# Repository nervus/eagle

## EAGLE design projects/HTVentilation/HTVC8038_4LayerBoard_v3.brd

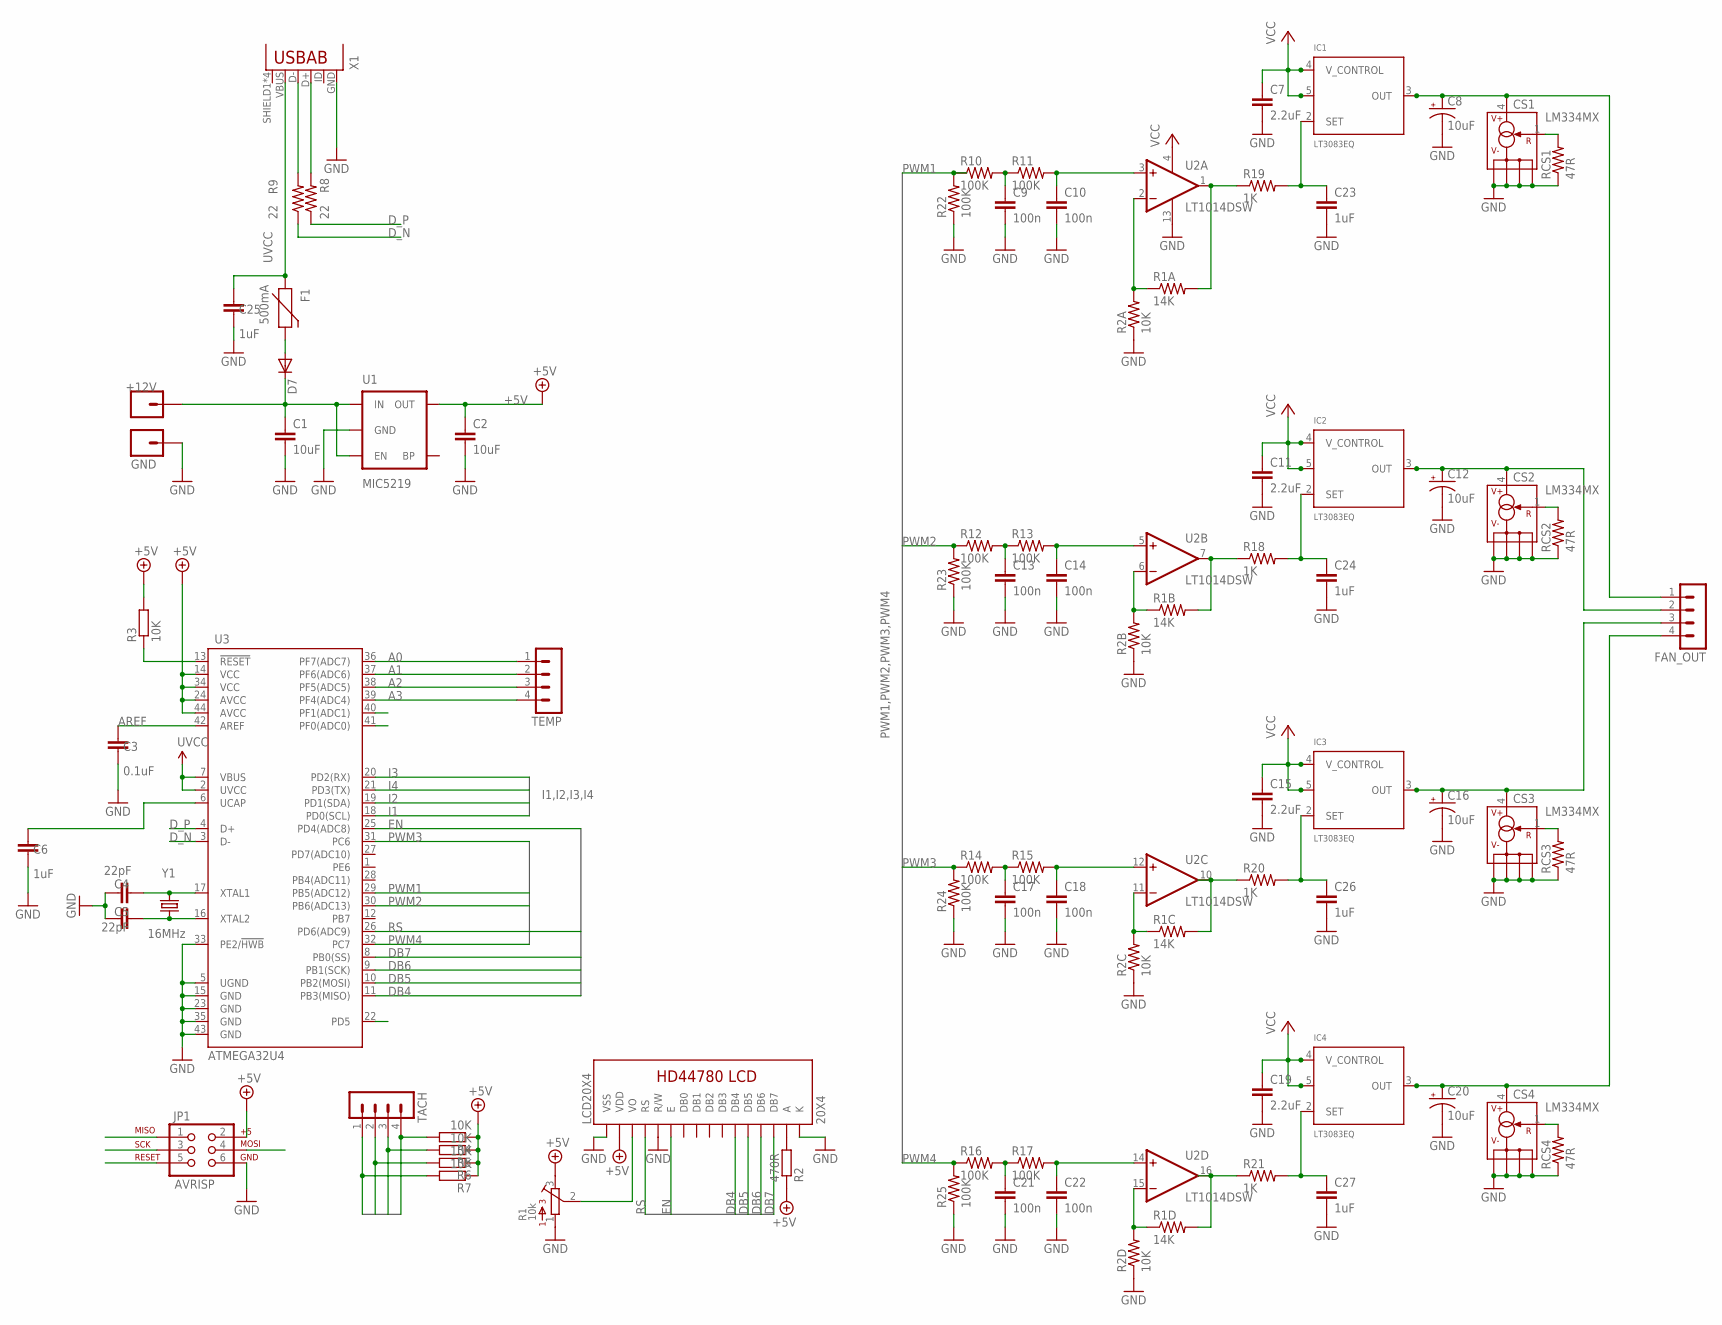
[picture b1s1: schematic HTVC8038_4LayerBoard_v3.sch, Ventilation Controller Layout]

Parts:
+12V: +12V; 1X01
C1, C2: 10uF; C1206
C3: 0.1uF; C0805
C4, C5: 22pF; C0805
C6, C23, C24, C25, C26, C27: 1uF; C0805
C7, C11, C15, C19: 2.2uF; C1206
C8, C12, C16, C20: 10uF; CT3528
C9, C10, C13, C14, C17, C18, C21, C22: 100n; C0805
CS1, CS2, CS3, CS4: LM334MX; SO08
D7: DIODESOD; SOD-323
F1: 500mA; PTC-1206
FAN_OUT: MA04-1
GND: GND; 1X01
IC1, IC2, IC3, IC4: LT3083EQ; DDPAK_TO263-5
JP1: AVRISP; 2X3-NS
LCD20X4: 20X4; LCD-20X4-4HOLES
R1: 10k; 3362P
R1A, R1B, R1C, R1D: 14K; R0603
R2: 470R; R0805
R2A, R2B, R2C, R2D, R3, R4, R5, R6, R7: 10K; R0805
R8, R9: 22; R0603
R10, R11, R12, R13, R14, R15, R16, R17, R22, R23, R24, R25: 100K; R0805
R18, R19, R20, R21: 1K; R0805
RCS1, RCS2, RCS3, RCS4: 47R; R0805
TACH: MA04-1
TEMP: MA04-1
U1: MIC5219; SOT23-5
U2: LT1014DSW; SO16W
U3: ATMEGA32U4; SPARKFUN-DIGITALIC_TQFP44
X1: USB-AB; USB-AB-MICRO-SMD
Y1: 16MHz; CRYSTAL-SMD-5X3

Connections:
+5V: C2.1, JP1.2, LCD20X4.P$2 (VDD), R1.3, R2.1, R3.2, R4.1, R5.1, R6.1, R7.1, U1.5 (OUT), U3.14 (VCC), U3.24 (AVCC), U3.34 (VCC), U3.44 (AVCC)
A0: TEMP.1, U3.36 (PF7(ADC7))
A1: TEMP.2, U3.37 (PF6(ADC6))
A2: TEMP.3, U3.38 (PF5(ADC5))
A3: TEMP.4, U3.39 (PF4(ADC4))
A4: U3.40 (PF1(ADC1))
A5: U3.41 (PF0(ADC0))
AREF: C3.2, U3.42 (AREF)
DB4: JP1.1, LCD20X4.P$11 (DB4), U3.11 (PB3(MISO))
DB5: JP1.4, LCD20X4.P$12 (DB5), U3.10 (PB2(MOSI))
DB6: JP1.3, LCD20X4.P$13 (DB6), U3.9 (PB1(SCK))
DB7: LCD20X4.P$14 (DB7), U3.8 (PB0(SS))
D_N: R9.1, U3.3 (D-)
D_P: R8.1, U3.4 (D+)
EN: LCD20X4.P$6 (E), U3.25 (PD4(ADC8))
GND: C1.2, C2.2, C3.1, C4.2, C5.2, C6.1, C7.2, C8.-, C9.2, C10.2, C11.2, C12.-, C13.2, C14.2, C15.2, C16.-, C17.2, C18.2, C19.2, C20.-, C21.2, C22.2, C23.2, C24.2, C25.1, C26.2, C27.2, CS1.2 (V-), CS1.3 (V-), CS1.6 (V-), CS1.7 (V-), CS2.2 (V-), CS2.3 (V-), CS2.6 (V-), CS2.7 (V-), CS3.2 (V-), CS3.3 (V-), CS3.6 (V-), CS3.7 (V-), CS4.2 (V-), CS4.3 (V-), CS4.6 (V-), CS4.7 (V-), GND.1, JP1.6, LCD20X4.P$1 (VSS), LCD20X4.P$5 (R/W), LCD20X4.P$16 (K), R1.1, R2A.1, R2B.1, R2C.1, R2D.1, R22.1, R23.1, R24.1, R25.1, RCS1.1, RCS2.1, RCS3.1, RCS4.1, U1.2 (GND), U2.13 (V-), U3.5 (UGND), U3.15 (GND), U3.23 (GND), U3.33 (PE2/!HWB), U3.35 (GND), U3.43 (GND), X1.GND
I1: R7.2, TACH.1, U3.18 (PD0(SCL))
I2: R6.2, TACH.2, U3.19 (PD1(SDA))
I3: R5.2, TACH.3, U3.20 (PD2(RX))
I4: R4.2, TACH.4, U3.21 (PD3(TX))
unnamed: R1A.1, R2A.2, U2.2 (-IN)
unnamed: R1B.1, R2B.2, U2.6 (-IN)
unnamed: R1C.1, R2C.2, U2.11 (-IN)
unnamed: R1D.1, R2D.2, U2.15 (-IN)
unnamed: C9.1, R10.2, R11.1
unnamed: C13.1, R12.2, R13.1
unnamed: LCD20X4.P$3 (VO), R1.2
unnamed: LCD20X4.P$15 (A), R2.2
unnamed: C5.1, U3.16 (XTAL2), Y1.1
unnamed: C4.1, U3.17 (XTAL1), Y1.3 (2)
unnamed: D7.2 (A), F1.2
unnamed: C6.2, U3.6 (UCAP)
unnamed: C17.1, R14.2, R15.1
unnamed: C21.1, R16.2, R17.1
unnamed: CS1.1 (R), RCS1.2
unnamed: CS2.1 (R), RCS2.2
unnamed: CS3.1 (R), RCS3.2
unnamed: CS4.1 (R), RCS4.2
unnamed: C27.1, IC4.2 (SET), R21.2
unnamed: C23.1, IC1.2 (SET), R19.2
unnamed: R1B.2, R18.1, U2.7 (OUT)
unnamed: C26.1, IC3.2 (SET), R20.2
OPAMP1: C10.1, R11.2, U2.3 (+IN)
OPAMP2: C14.1, R13.2, U2.5 (+IN)
OPAMP3: C18.1, R15.2, U2.12 (+IN)
OPAMP4: C22.1, R17.2, U2.14 (+IN)
OUT1: C8.+, CS1.4 (V+), FAN_OUT.1, IC1.3 (OUT), IC1.6 (OUT)
OUT2: C12.+, CS2.4 (V+), FAN_OUT.2, IC2.3 (OUT), IC2.6 (OUT)
OUT3: C16.+, CS3.4 (V+), FAN_OUT.3, IC3.3 (OUT), IC3.6 (OUT)
OUT4: C20.+, CS4.4 (V+), FAN_OUT.4, IC4.3 (OUT), IC4.6 (OUT)
PWM1: R10.1, R22.2, U3.29 (PB5(ADC12))
PWM2: R12.1, R23.2, U3.30 (PB6(ADC13))
PWM3: R14.1, R24.2, U3.31 (PC6)
PWM4: R16.1, R25.2, U3.32 (PC7)
RESET: JP1.5, R3.1, U3.13 (!RESET)
RS: LCD20X4.P$4 (RS), U3.26 (PD6(ADC9))
SET1: R1A.2, R19.1, U2.1 (OUT)
SET2: C24.1, IC2.2 (SET), R18.2
SET3: R1C.2, R20.1, U2.10 (OUT)
SET4: R1D.2, R21.1, U2.16 (OUT)
TXLED: U3.22 (PD5)
USB_N: R9.2, X1.D-
USB_P: R8.2, X1.D+
UVCC: C25.2, F1.1, U3.2 (UVCC), U3.7 (VBUS), X1.VBUS
VCC: +12V.1, C1.1, C7.1, C11.1, C15.1, C19.1, D7.1 (C), IC1.4 (V_CONTROL), IC1.5 (IN), IC2.4 (V_CONTROL), IC2.5 (IN), IC3.4 (V_CONTROL), IC3.5 (IN), IC4.4 (V_CONTROL), IC4.5 (IN), U1.1 (IN), U1.3 (EN), U2.4 (V+)

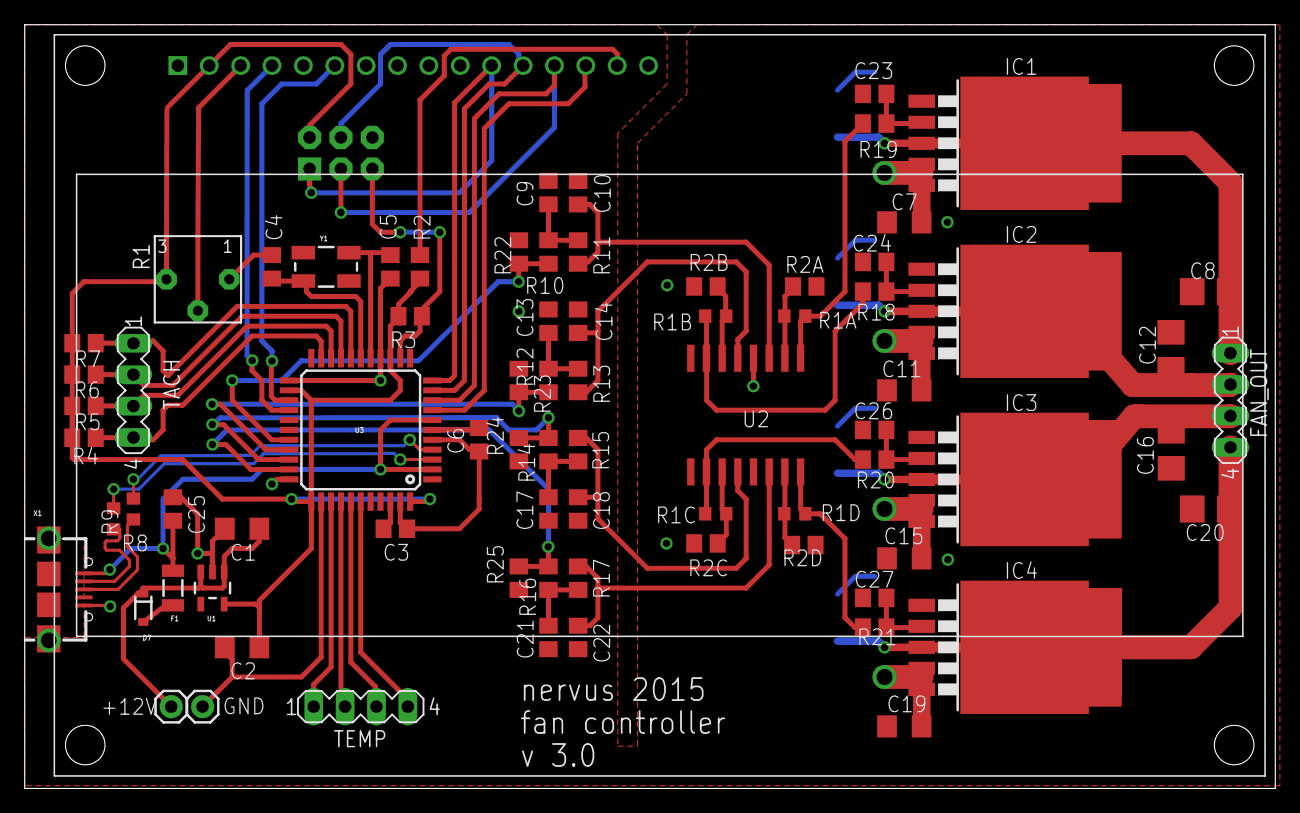
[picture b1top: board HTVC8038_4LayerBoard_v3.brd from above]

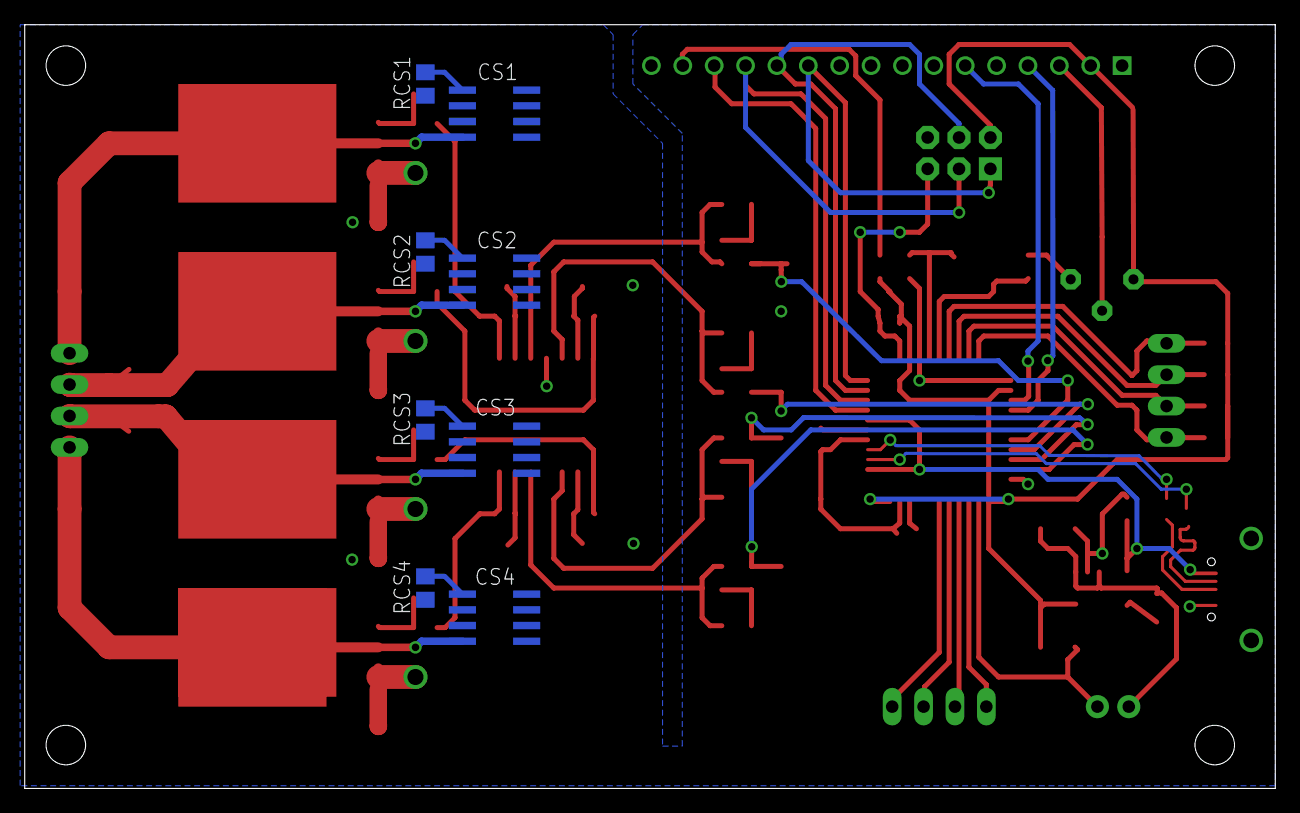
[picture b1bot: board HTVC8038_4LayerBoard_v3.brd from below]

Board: 4 copper layers, 101.2 x 61.8 mm, 86 parts (8 on the bottom side), 62 nets.

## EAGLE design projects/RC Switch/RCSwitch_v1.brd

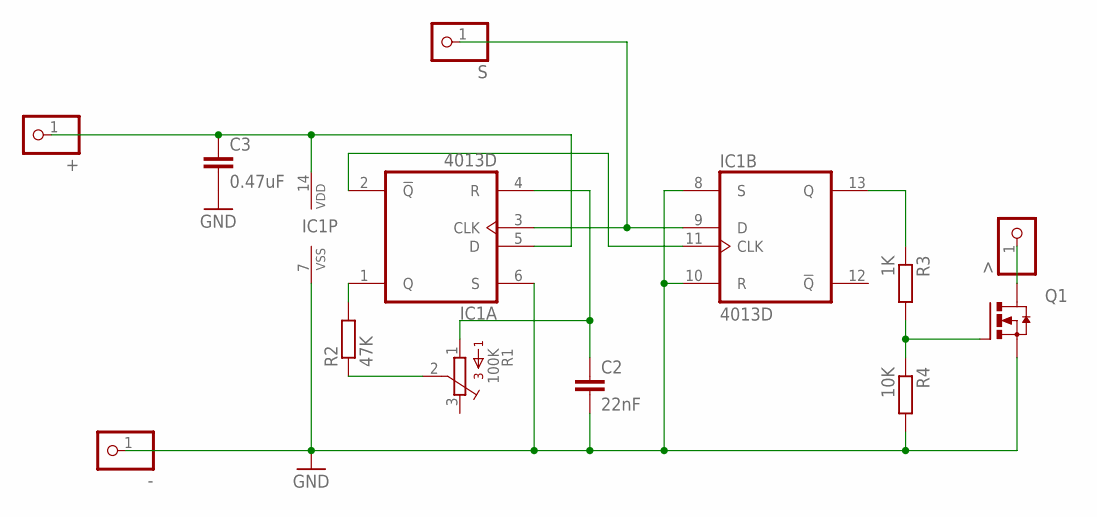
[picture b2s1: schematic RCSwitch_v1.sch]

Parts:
+: PINHD-1X1; 1X01
-: PINHD-1X1; 1X01
>: PINHD-1X1; 1X01
C2: 22nF; C3216
C3: 0.47uF; C3216
IC1: 4013D; SO14
Q1: IRF3704S; D2PACK
R1: 100K; 3386P
R2: 47K; R3225
R3: 1K; R3225
R4: 10K; R3225
S: PINHD-1X1; 1X01

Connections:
GND: -.1, C2.2, C3.2, IC1.6 (S), IC1.7 (VSS), IC1.8 (S), IC1.10 (R), Q1.3 (S), R4.2
unnamed: IC1.1 (Q), R2.2
unnamed: R1.2, R2.1
unnamed: C2.1, IC1.4 (R), R1.1
unnamed: IC1.13 (Q), R3.1
unnamed: IC1.3 (CLK), IC1.9 (D), S.1
unnamed: >.1, Q1.2 (D)
unnamed: IC1.2 (!Q), IC1.11 (CLK)
unnamed: +.1, C3.1, IC1.5 (D), IC1.14 (VDD)
OUTPUT: Q1.1 (G), R3.2, R4.1

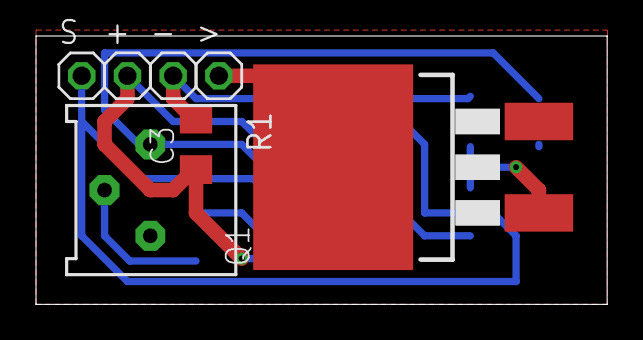
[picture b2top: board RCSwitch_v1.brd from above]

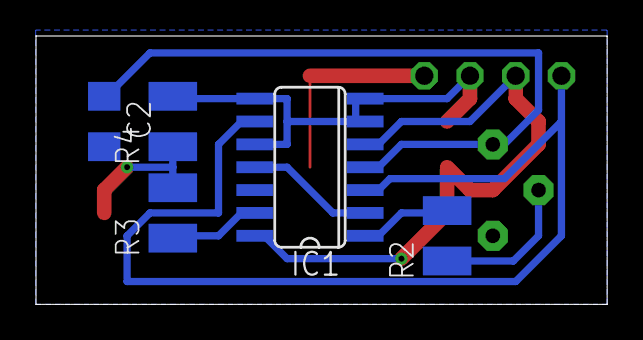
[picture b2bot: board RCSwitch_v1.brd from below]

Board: 2 copper layers, 31.7 x 14.9 mm, 12 parts (5 on the bottom side), 10 nets.

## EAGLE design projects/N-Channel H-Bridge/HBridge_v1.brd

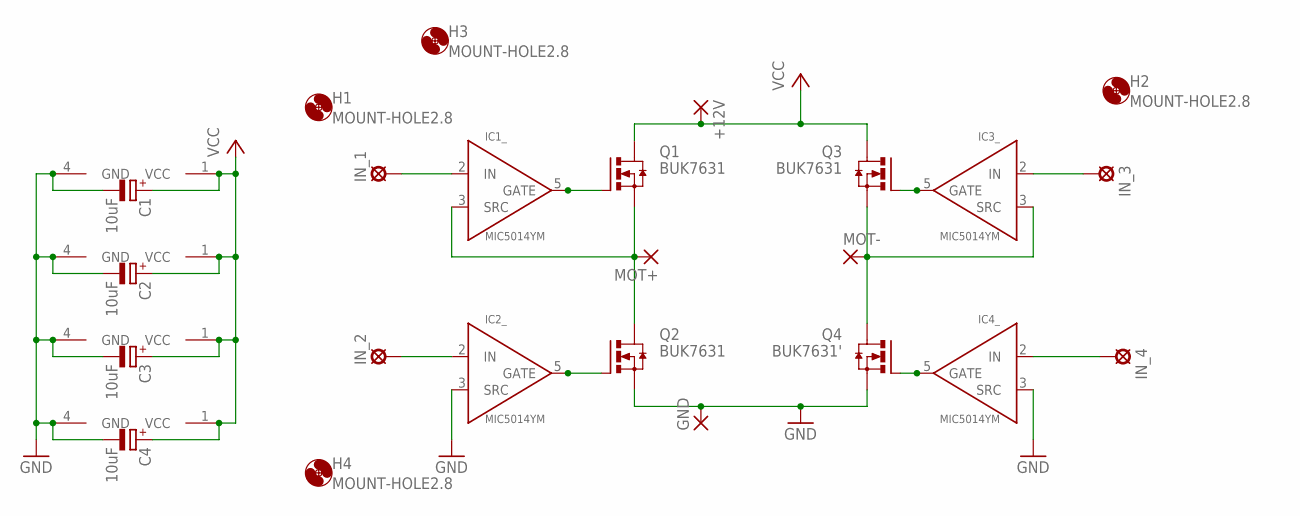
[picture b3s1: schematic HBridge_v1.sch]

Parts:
+12V: WIREPAD4,16O1,6; 4,16O1,6
C1, C2, C3, C4: 10uF; UD-4X5,8_NICHICON
GND: WIREPAD4,16O1,6; 4,16O1,6
H1, H2, H3, H4: MOUNT-HOLE2.8; 2,8
IC1, IC2, IC3, IC4: MIC5014YM; SO8
IN_1, IN_2, IN_3, IN_4: LSP11
MOT+: WIREPAD4,16O1,6; 4,16O1,6
MOT-: WIREPAD4,16O1,6; 4,16O1,6
Q1, Q2, Q3: BUK7631; D2PAK_TO263
Q4: BUK7631'; D2PAK_TO263

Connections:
GND: C1.-, C2.-, C3.-, C4.-, GND.1, IC1.4 (GND), IC2.3 (SRC), IC2.4 (GND), IC3.4 (GND), IC4.3 (SRC), IC4.4 (GND), Q2.3 (S), Q4.3 (S)
MOT+: IC1.3 (SRC), MOT+.1, Q1.3 (S), Q2.4 (D)
MOT-: IC3.3 (SRC), MOT-.1, Q3.3 (S), Q4.4 (D)
unnamed: IC4.2 (IN), IN_4.MP
unnamed: IC3.5 (GATE), Q3.1 (G)
unnamed: IC1.2 (IN), IN_1.MP
unnamed: IC3.2 (IN), IN_3.MP
unnamed: IC2.2 (IN), IN_2.MP
unnamed: IC1.5 (GATE), Q1.1 (G)
unnamed: IC4.5 (GATE), Q4.1 (G)
unnamed: IC2.5 (GATE), Q2.1 (G)
VCC: +12V.1, C1.+, C2.+, C3.+, C4.+, IC1.1 (VCC), IC2.1 (VCC), IC3.1 (VCC), IC4.1 (VCC), Q1.4 (D), Q3.4 (D)

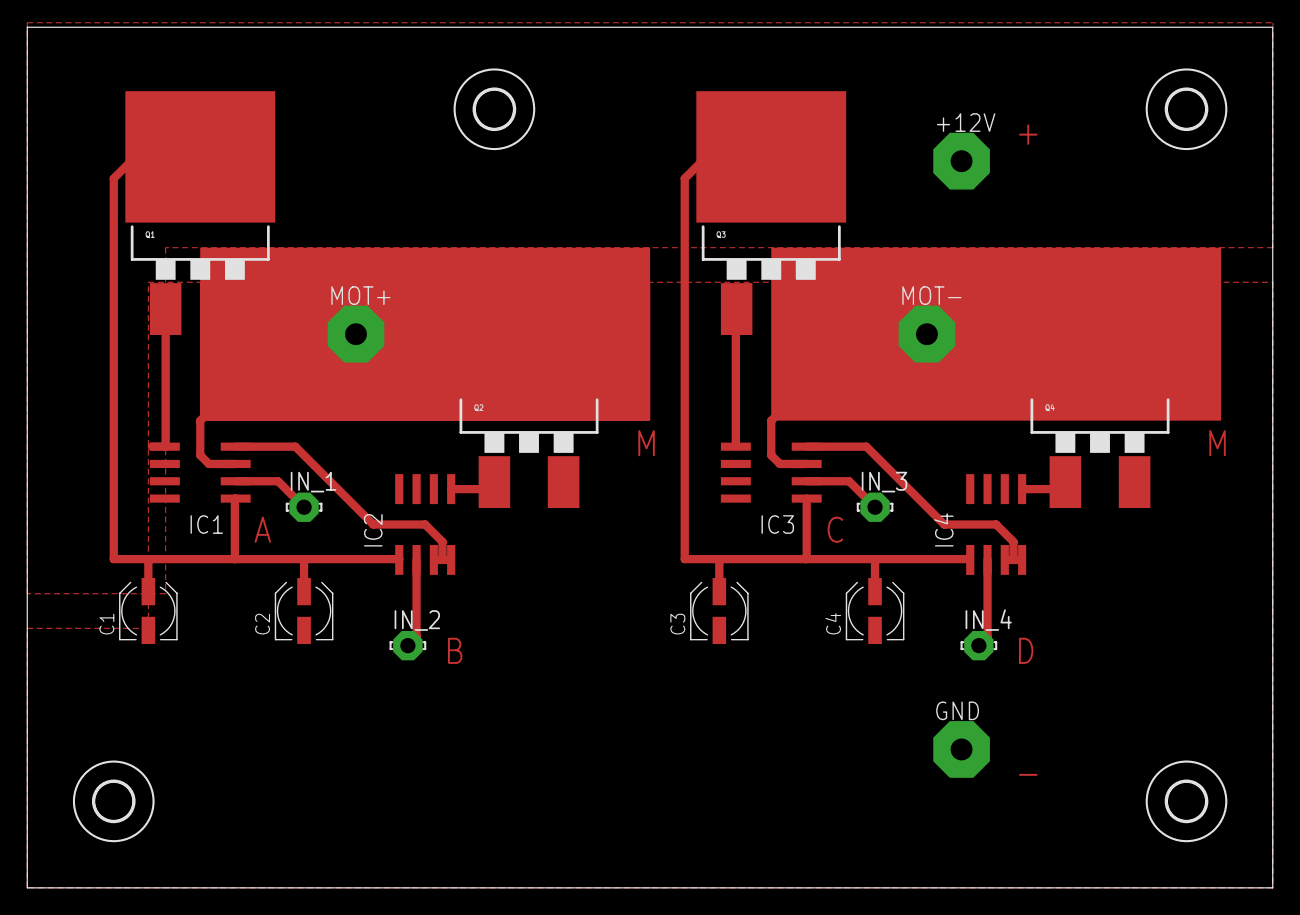
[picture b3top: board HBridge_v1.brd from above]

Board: 2 copper layers, 91.4 x 63.2 mm, 24 parts (0 on the bottom side), 12 nets.

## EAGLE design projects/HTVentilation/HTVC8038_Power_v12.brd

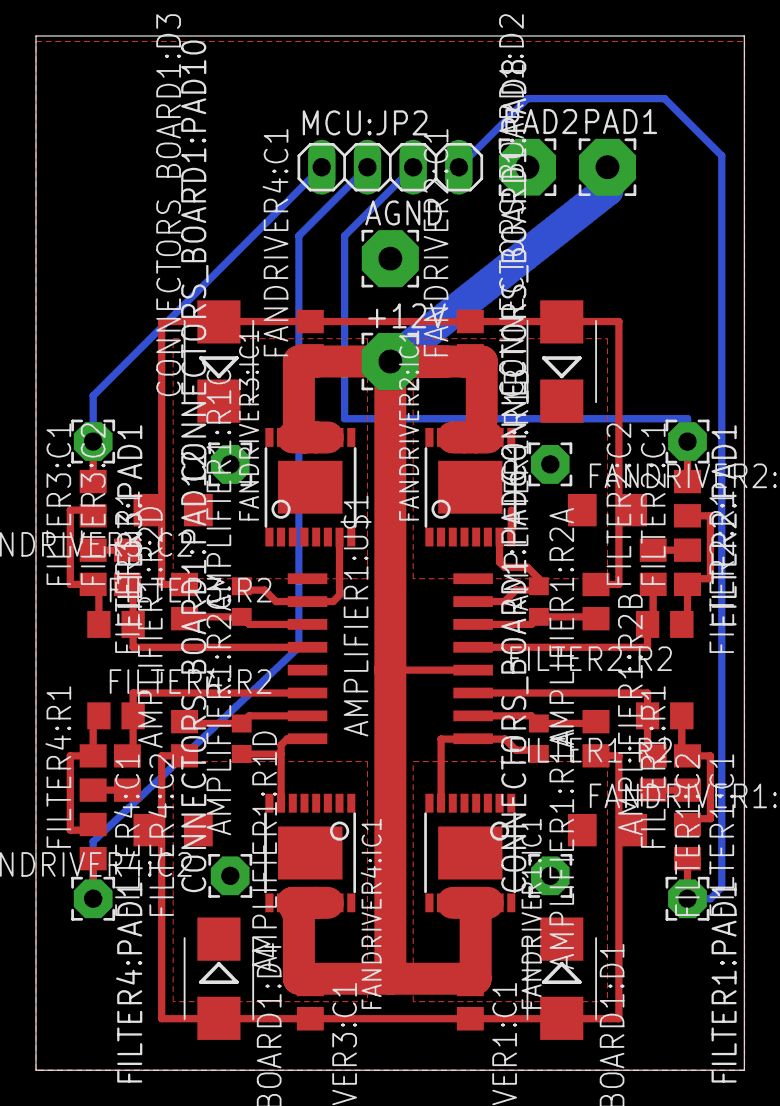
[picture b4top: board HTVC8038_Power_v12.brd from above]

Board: 2 copper layers, 39.3 x 57.5 mm, 54 parts (0 on the bottom side), 26 nets.

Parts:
+12V: 3,17/1,3
AGND: 3,17/1,3
AMPLIFIER1:R1A, AMPLIFIER1:R1B, AMPLIFIER1:R1C, AMPLIFIER1:R1D: 14K; R0603
AMPLIFIER1:R2A, AMPLIFIER1:R2B, AMPLIFIER1:R2C, AMPLIFIER1:R2D: 10K; R0805
AMPLIFIER1:U$1: LT1014; SO16W
CONNECTORS_BOARD1:D1, CONNECTORS_BOARD1:D2, CONNECTORS_BOARD1:D3, CONNECTORS_BOARD1:D4: MBRS240LT3; SMB-403A
CONNECTORS_BOARD1:PAD6, CONNECTORS_BOARD1:PAD8, CONNECTORS_BOARD1:PAD10, CONNECTORS_BOARD1:PAD12: 2,15/1,0
FANDRIVER1:C1, FANDRIVER2:C1, FANDRIVER3:C1, FANDRIVER4:C1: 2.2uF; C0805
FANDRIVER1:C2, FANDRIVER2:C2, FANDRIVER3:C2, FANDRIVER4:C2: 10uF; C1206
FANDRIVER1:IC1, FANDRIVER2:IC1, FANDRIVER3:IC1, FANDRIVER4:IC1: LT3083EFE; TSSOP16EXP
FILTER1:C1, FILTER1:C2, FILTER2:C1, FILTER2:C2, FILTER3:C1, FILTER3:C2, FILTER4:C1, FILTER4:C2: 100n; C0805
FILTER1:PAD1, FILTER2:PAD1, FILTER3:PAD1, FILTER4:PAD1: 2,15/1,0
FILTER1:R1, FILTER1:R2, FILTER2:R1, FILTER2:R2, FILTER3:R1, FILTER3:R2, FILTER4:R1, FILTER4:R2: 100K; R0805
MCU:JP2: 1X04
PAD1, PAD2: 3,17/1,3

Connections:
AGND: AGND.1, AMPLIFIER1:R2A.1, AMPLIFIER1:R2B.1, AMPLIFIER1:R2C.1, AMPLIFIER1:R2D.1, AMPLIFIER1:U$1.13, CONNECTORS_BOARD1:D1.A, CONNECTORS_BOARD1:D2.A, CONNECTORS_BOARD1:D3.A, CONNECTORS_BOARD1:D4.A, FANDRIVER1:C1.2, FANDRIVER1:C2.2, FANDRIVER2:C1.2, FANDRIVER2:C2.2, FANDRIVER3:C1.2, FANDRIVER3:C2.2, FANDRIVER4:C1.2, FANDRIVER4:C2.2, FILTER1:C1.2, FILTER1:C2.2, FILTER2:C1.2, FILTER2:C2.2, FILTER3:C1.2, FILTER3:C2.2, FILTER4:C1.2, FILTER4:C2.2, PAD2.1
AMPLIFIER1:N$1: AMPLIFIER1:R1B.1, AMPLIFIER1:R2B.2, AMPLIFIER1:U$1.6
AMPLIFIER1:N$2: AMPLIFIER1:R1C.1, AMPLIFIER1:R2C.2, AMPLIFIER1:U$1.11
AMPLIFIER1:N$3: AMPLIFIER1:R1D.1, AMPLIFIER1:R2D.2, AMPLIFIER1:U$1.15
AMPLIFIER1:N$9: AMPLIFIER1:R1A.1, AMPLIFIER1:R2A.2, AMPLIFIER1:U$1.2
FILTER1:N$8: FILTER1:C1.1, FILTER1:R1.2, FILTER1:R2.1
FILTER2:N$8: FILTER2:C1.1, FILTER2:R1.2, FILTER2:R2.1
FILTER3:N$8: FILTER3:C1.1, FILTER3:R1.2, FILTER3:R2.1
FILTER4:N$8: FILTER4:C1.1, FILTER4:R1.2, FILTER4:R2.1
unnamed: CONNECTORS_BOARD1:D4.C, CONNECTORS_BOARD1:PAD12.1, FANDRIVER4:C2.1, FANDRIVER4:IC1.1, FANDRIVER4:IC1.2, FANDRIVER4:IC1.3, FANDRIVER4:IC1.4, FANDRIVER4:IC1.5, FANDRIVER4:IC1.6, FANDRIVER4:IC1.8, FANDRIVER4:IC1.9, FANDRIVER4:IC1.16, FANDRIVER4:IC1.EXP
unnamed: CONNECTORS_BOARD1:D3.C, CONNECTORS_BOARD1:PAD10.1, FANDRIVER3:C2.1, FANDRIVER3:IC1.1, FANDRIVER3:IC1.2, FANDRIVER3:IC1.3, FANDRIVER3:IC1.4, FANDRIVER3:IC1.5, FANDRIVER3:IC1.6, FANDRIVER3:IC1.8, FANDRIVER3:IC1.9, FANDRIVER3:IC1.16, FANDRIVER3:IC1.EXP
unnamed: CONNECTORS_BOARD1:D2.C, CONNECTORS_BOARD1:PAD8.1, FANDRIVER2:C2.1, FANDRIVER2:IC1.1, FANDRIVER2:IC1.2, FANDRIVER2:IC1.3, FANDRIVER2:IC1.4, FANDRIVER2:IC1.5, FANDRIVER2:IC1.6, FANDRIVER2:IC1.8, FANDRIVER2:IC1.9, FANDRIVER2:IC1.16, FANDRIVER2:IC1.EXP
unnamed: CONNECTORS_BOARD1:D1.C, CONNECTORS_BOARD1:PAD6.1, FANDRIVER1:C2.1, FANDRIVER1:IC1.1, FANDRIVER1:IC1.2, FANDRIVER1:IC1.3, FANDRIVER1:IC1.4, FANDRIVER1:IC1.5, FANDRIVER1:IC1.6, FANDRIVER1:IC1.8, FANDRIVER1:IC1.9, FANDRIVER1:IC1.16, FANDRIVER1:IC1.EXP
unnamed: FILTER1:PAD1.1, FILTER1:R1.1, MCU:JP2.4
unnamed: FILTER2:PAD1.1, FILTER2:R1.1, MCU:JP2.3
unnamed: FILTER3:PAD1.1, FILTER3:R1.1, MCU:JP2.1
unnamed: FILTER4:PAD1.1, FILTER4:R1.1, MCU:JP2.2
unnamed: AMPLIFIER1:U$1.3, FILTER1:C2.1, FILTER1:R2.2
unnamed: AMPLIFIER1:U$1.5, FILTER2:C2.1, FILTER2:R2.2
unnamed: AMPLIFIER1:U$1.12, FILTER3:C2.1, FILTER3:R2.2
unnamed: AMPLIFIER1:U$1.14, FILTER4:C2.1, FILTER4:R2.2
unnamed: AMPLIFIER1:R1A.2, AMPLIFIER1:U$1.1, FANDRIVER1:IC1.7
unnamed: AMPLIFIER1:R1B.2, AMPLIFIER1:U$1.7, FANDRIVER2:IC1.7
unnamed: AMPLIFIER1:R1C.2, AMPLIFIER1:U$1.10, FANDRIVER3:IC1.7
unnamed: AMPLIFIER1:R1D.2, AMPLIFIER1:U$1.16, FANDRIVER4:IC1.7
VCC: +12V.1, AMPLIFIER1:U$1.4, FANDRIVER1:C1.1, FANDRIVER1:IC1.10, FANDRIVER1:IC1.11, FANDRIVER1:IC1.12, FANDRIVER1:IC1.13, FANDRIVER1:IC1.14, FANDRIVER1:IC1.15, FANDRIVER2:C1.1, FANDRIVER2:IC1.10, FANDRIVER2:IC1.11, FANDRIVER2:IC1.12, FANDRIVER2:IC1.13, FANDRIVER2:IC1.14, FANDRIVER2:IC1.15, FANDRIVER3:C1.1, FANDRIVER3:IC1.10, FANDRIVER3:IC1.11, FANDRIVER3:IC1.12, FANDRIVER3:IC1.13, FANDRIVER3:IC1.14, FANDRIVER3:IC1.15, FANDRIVER4:C1.1, FANDRIVER4:IC1.10, FANDRIVER4:IC1.11, FANDRIVER4:IC1.12, FANDRIVER4:IC1.13, FANDRIVER4:IC1.14, FANDRIVER4:IC1.15, PAD1.1

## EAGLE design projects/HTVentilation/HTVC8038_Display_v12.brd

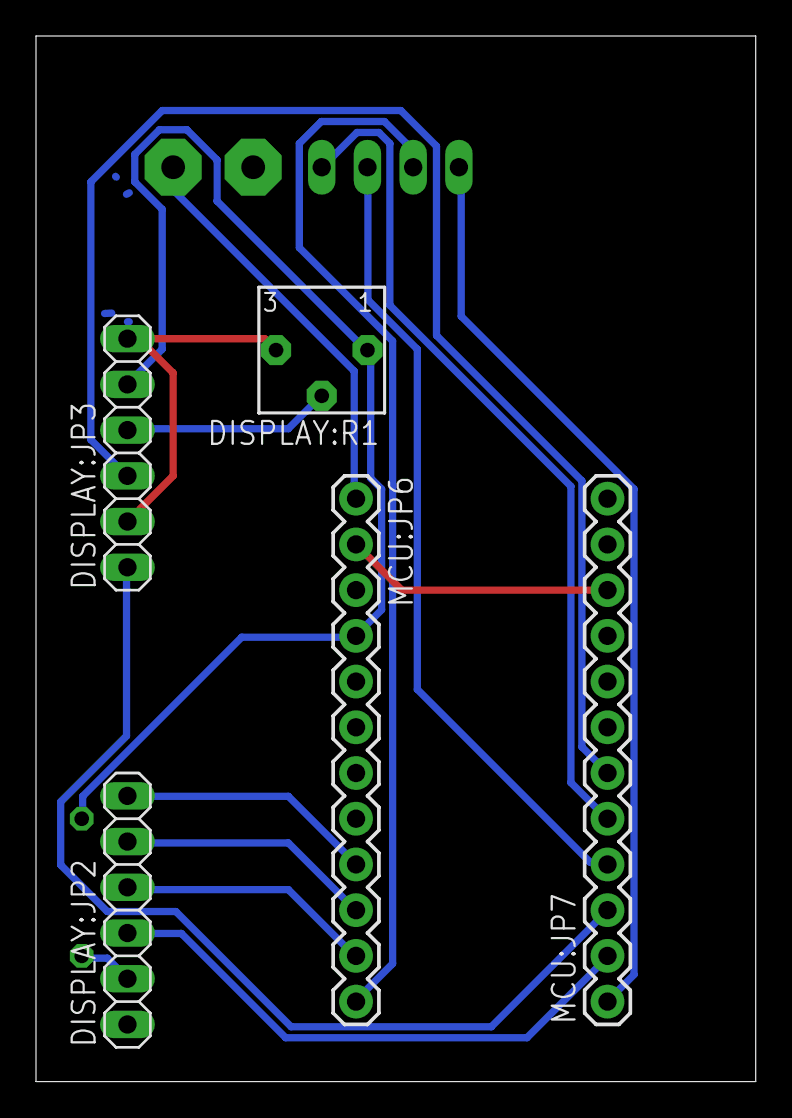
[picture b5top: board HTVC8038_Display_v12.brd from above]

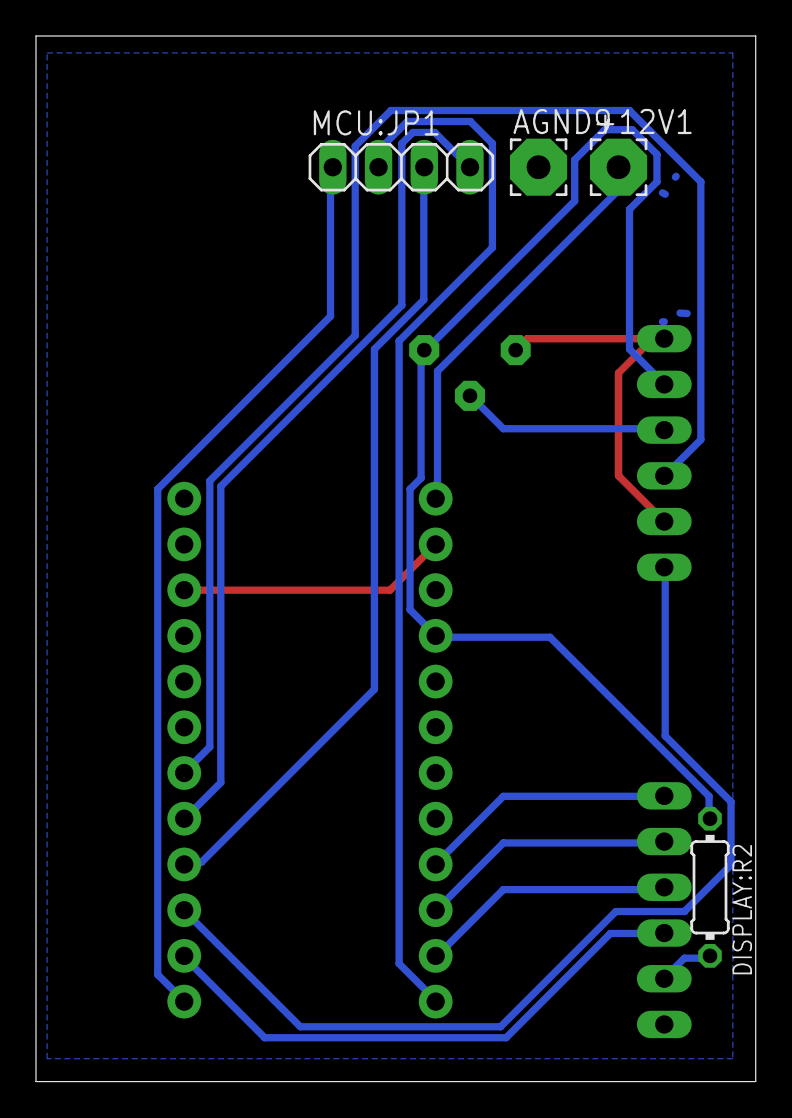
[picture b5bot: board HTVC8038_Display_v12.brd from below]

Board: 2 copper layers, 40.0 x 58.1 mm, 9 parts (4 on the bottom side), 15 nets.

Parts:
+12V1: 3,17/1,3
AGND9: 3,17/1,3
DISPLAY:JP2, DISPLAY:JP3: 1X06
DISPLAY:R1: 10k; 3362P
DISPLAY:R2: 470R; 0204/7
MCU:JP1: 1X04
MCU:JP6, MCU:JP7: 1X12

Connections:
+5V: DISPLAY:JP3.5, DISPLAY:R1.1, DISPLAY:R2.1, MCU:JP6.4
AGND: AGND9.1, DISPLAY:JP2.1, DISPLAY:JP3.2, DISPLAY:JP3.6, DISPLAY:R1.3, MCU:JP6.2, MCU:JP7.9, MCU:JP7.10
DISPLAY:N$1: DISPLAY:JP3.4, DISPLAY:R1.2
DISPLAY:N$2: DISPLAY:JP2.2, DISPLAY:R2.2
unnamed: DISPLAY:JP3.3, MCU:JP7.6
unnamed: DISPLAY:JP3.1, MCU:JP7.3
unnamed: DISPLAY:JP2.6, MCU:JP6.9
unnamed: DISPLAY:JP2.5, MCU:JP6.10
unnamed: DISPLAY:JP2.4, MCU:JP6.11
unnamed: DISPLAY:JP2.3, MCU:JP7.2
unnamed: MCU:JP1.4, MCU:JP7.5
unnamed: MCU:JP1.3, MCU:JP7.4
unnamed: MCU:JP1.1, MCU:JP7.1
unnamed: MCU:JP1.2, MCU:JP6.12
VCC: +12V1.1, MCU:JP6.1

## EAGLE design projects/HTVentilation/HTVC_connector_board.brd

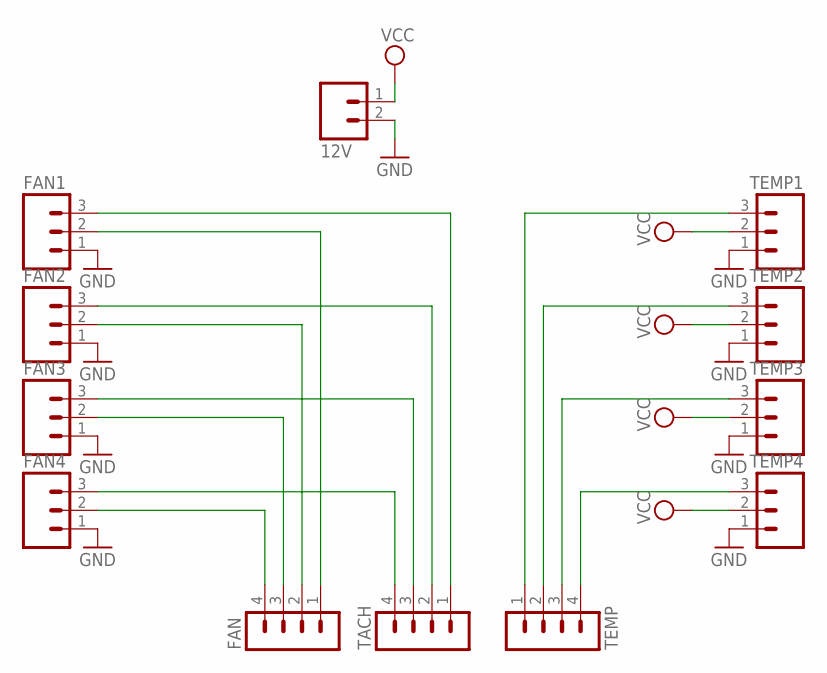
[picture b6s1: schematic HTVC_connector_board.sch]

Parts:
12V: M02PTH; 1X02
FAN: MA04-1
FAN1, FAN2, FAN3, FAN4: M03POLAR; MOLEX-1X3
TACH: MA04-1
TEMP: MA04-1
TEMP1, TEMP2, TEMP3, TEMP4: M03POLAR; MOLEX-1X3

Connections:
GND: 12V.2, FAN1.1, FAN2.1, FAN3.1, FAN4.1, TEMP1.1, TEMP2.1, TEMP3.1, TEMP4.1
unnamed: FAN1.3, TACH.1
unnamed: FAN2.3, TACH.2
unnamed: FAN3.3, TACH.3
unnamed: FAN4.3, TACH.4
unnamed: FAN.1, FAN1.2
unnamed: FAN.2, FAN2.2
unnamed: FAN.3, FAN3.2
unnamed: FAN.4, FAN4.2
unnamed: TEMP.1, TEMP1.3
unnamed: TEMP.2, TEMP2.3
unnamed: TEMP.3, TEMP3.3
unnamed: TEMP.4, TEMP4.3
VCC: 12V.1, TEMP1.2, TEMP2.2, TEMP3.2, TEMP4.2

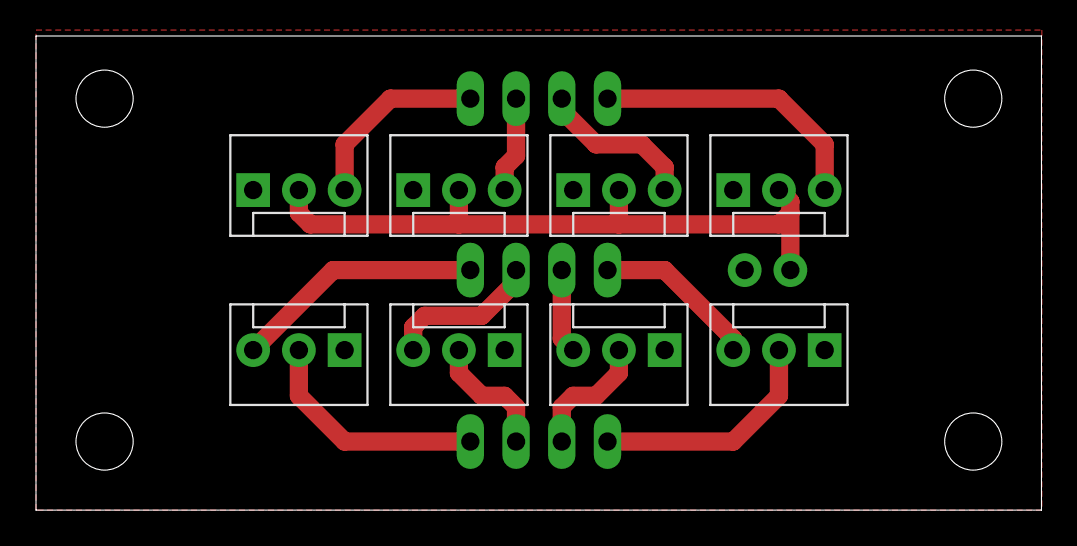
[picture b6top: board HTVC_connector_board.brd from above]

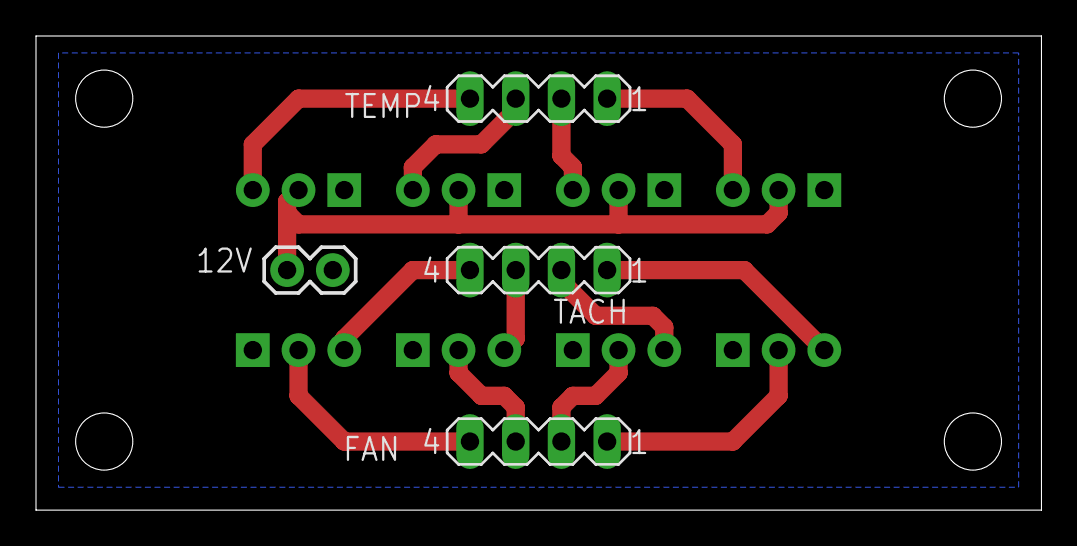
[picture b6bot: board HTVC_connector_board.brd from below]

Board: 2 copper layers, 55.9 x 26.3 mm, 12 parts (4 on the bottom side), 14 nets.

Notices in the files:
parts and their libraries:
SparkFun-Connectors: Licensing: Creative Commons ShareAlike 4.0 International - https://creativecommons.org/licenses/by-sa/4.0
